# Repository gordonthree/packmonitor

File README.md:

# Smart battery power monitor project

### A slim circuit board for managing charge and discharge of multi-cell LiFePo4 battery packs. Intended to track state of charge by coulomb counting and prevent battery pack damage from over discharge, over current and over temperature conditions.

## Goals:

1. Monitor and record total amperage in and out
2. Monitor and record temperature, ideally three places
3. Monitor and record pack voltage
4. Provide under-voltage disconnect
5. Provide over-temperature disconnect

## Features:
1. Atmel AVR: AVR128DA32 or AVR128DA28
1. Hall effect current sensor: TMCS1108
   * ~~Check my inventory for ACS7xx sensors!~~
3. FRAM for local data caching: I2C FM24C64B
4. Precision ADC: I2C NAU7802
5. Hot swap buffer: I2C TCA4311a / PCA9508 (pin compatible)
1. ~~Host side i2c mux: PCA9545A~~ (hope to avoid)
6. Max PCB width 18mm
7. Precision fixed resistor for thermistors?
   * Thermistors: NRL1504F3950B1F
   * Thermistors connect to uC ADC, 12 bit good 'nuff
8. ~~Power selector IC: AP2411~~
9. Low Iq power supply for battery side, switching, not sure yet!
10. ~~SMT button for battiery status,~~ not sure yet, board is pretty tight

## Connectors:

1. Battery side
   * Battery In and Out (14 ga) - WAGO screw cage
   * 6-pin jst-xh vertical for three thermistors
1. Upstream interface: I2C
   * JST-xh 6-pin connector +5v, GND, SCL, GND, SDA, GND
   * TCA4311 on battery side
   * I2C switch on host side (might not need)

## Indicators (not likely):

1. Bus controlled:
   * Bus power (from vcc)
   * Bus active (from CS line)
2. uC controlled:
   * Battery SOC (three leds)
   * Battery health (red/green)

## Client Commands:

* See registers.md for addressing and more details

## Questions:

1. Data logging without a RTC?
  * Chip seems to keep time well enough with occasional updates from master
1. High side or low side disconnect?

## Resources:

#### ATMega4808:

* [https://www.digikey.com/en/products/detail/microchip-technology/ATMEGA4808-AUR/10444912](https://www.digikey.com/en/products/detail/microchip-technology/ATMEGA4808-AUR/10444912)
* [https://ww1.microchip.com/downloads/en/DeviceDoc/ATmega4808-09-DataSheet-DS40002173C.pdf](https://ww1.microchip.com/downloads/en/DeviceDoc/ATmega4808-09-DataSheet-DS40002173C.pdf)
* [https://github.com/MCUdude/MegaCoreX#pinout](https://github.com/MCUdude/MegaCoreX#pinout)

#### Thermistor:

* [https://www.digikey.com/en/products/detail/eaton-electronics-division/NRL1504F3950B1F/15927588](https://www.digikey.com/en/products/detail/eaton-electronics-division/NRL1504F3950B1F/15927588)
* [https://www.maximintegrated.com/en/design/technical-documents/app-notes/1/1753.html](https://www.maximintegrated.com/en/design/technical-documents/app-notes/1/1753.html)
* [https://www.jameco.com/Jameco/workshop/TechTip/temperature-measurement-ntc-thermistors.html](https://www.jameco.com/Jameco/workshop/TechTip/temperature-measurement-ntc-thermistors.html)

#### Readng precise voltages:

* [https://skillbank.co.uk/arduino/measure.htm](https://skillbank.co.uk/arduino/measure.htm)

#### ATMEGA Arduino:

* [https://github.com/MCUdude/MegaCoreX](https://github.com/MCUdude/MegaCoreX)

#### AVR DA / DB / DD Series:

* [https://github.com/SpenceKonde/DxCore](https://github.com/SpenceKonde/DxCore)
#### Bootloader:

* [https://github.com/Optiboot/optiboot](https://github.com/Optiboot/optiboot)

#### FRAM:

* [FM24C64B](https://www.digikey.com/en/products/detail/cypress-semiconductor-corp/FM24C64B-GTR/3788931)

#### Hall Effect Sensor:

* [https://www.ti.com/product/TMCS1108](https://www.ti.com/product/TMCS1108)

#### Hot swap buffers:

* [https://www.digikey.com/en/products/detail/nxp-usa-inc/PCA9545AD-118/789953](https://www.digikey.com/en/products/detail/nxp-usa-inc/PCA9545AD-118/789953)

* [https://www.ti.com/product/TCA4311A?qgpn=tca4311a](https://www.ti.com/product/TCA4311A?qgpn=tca4311a)
#### Switching regulator (tiny):

* [https://www.diodes.com/assets/Datasheets/AP62200_AP62201_AP62200T.pdf](https://www.diodes.com/assets/Datasheets/AP62200_AP62201_AP62200T.pdf)

#### ADC:

* [https://www.nuvoton.com/export/resource-files/NAU7802%20Data%20Sheet%20V1.7.pdf](https://www.nuvoton.com/export/resource-files/NAU7802%20Data%20Sheet%20V1.7.pdf)

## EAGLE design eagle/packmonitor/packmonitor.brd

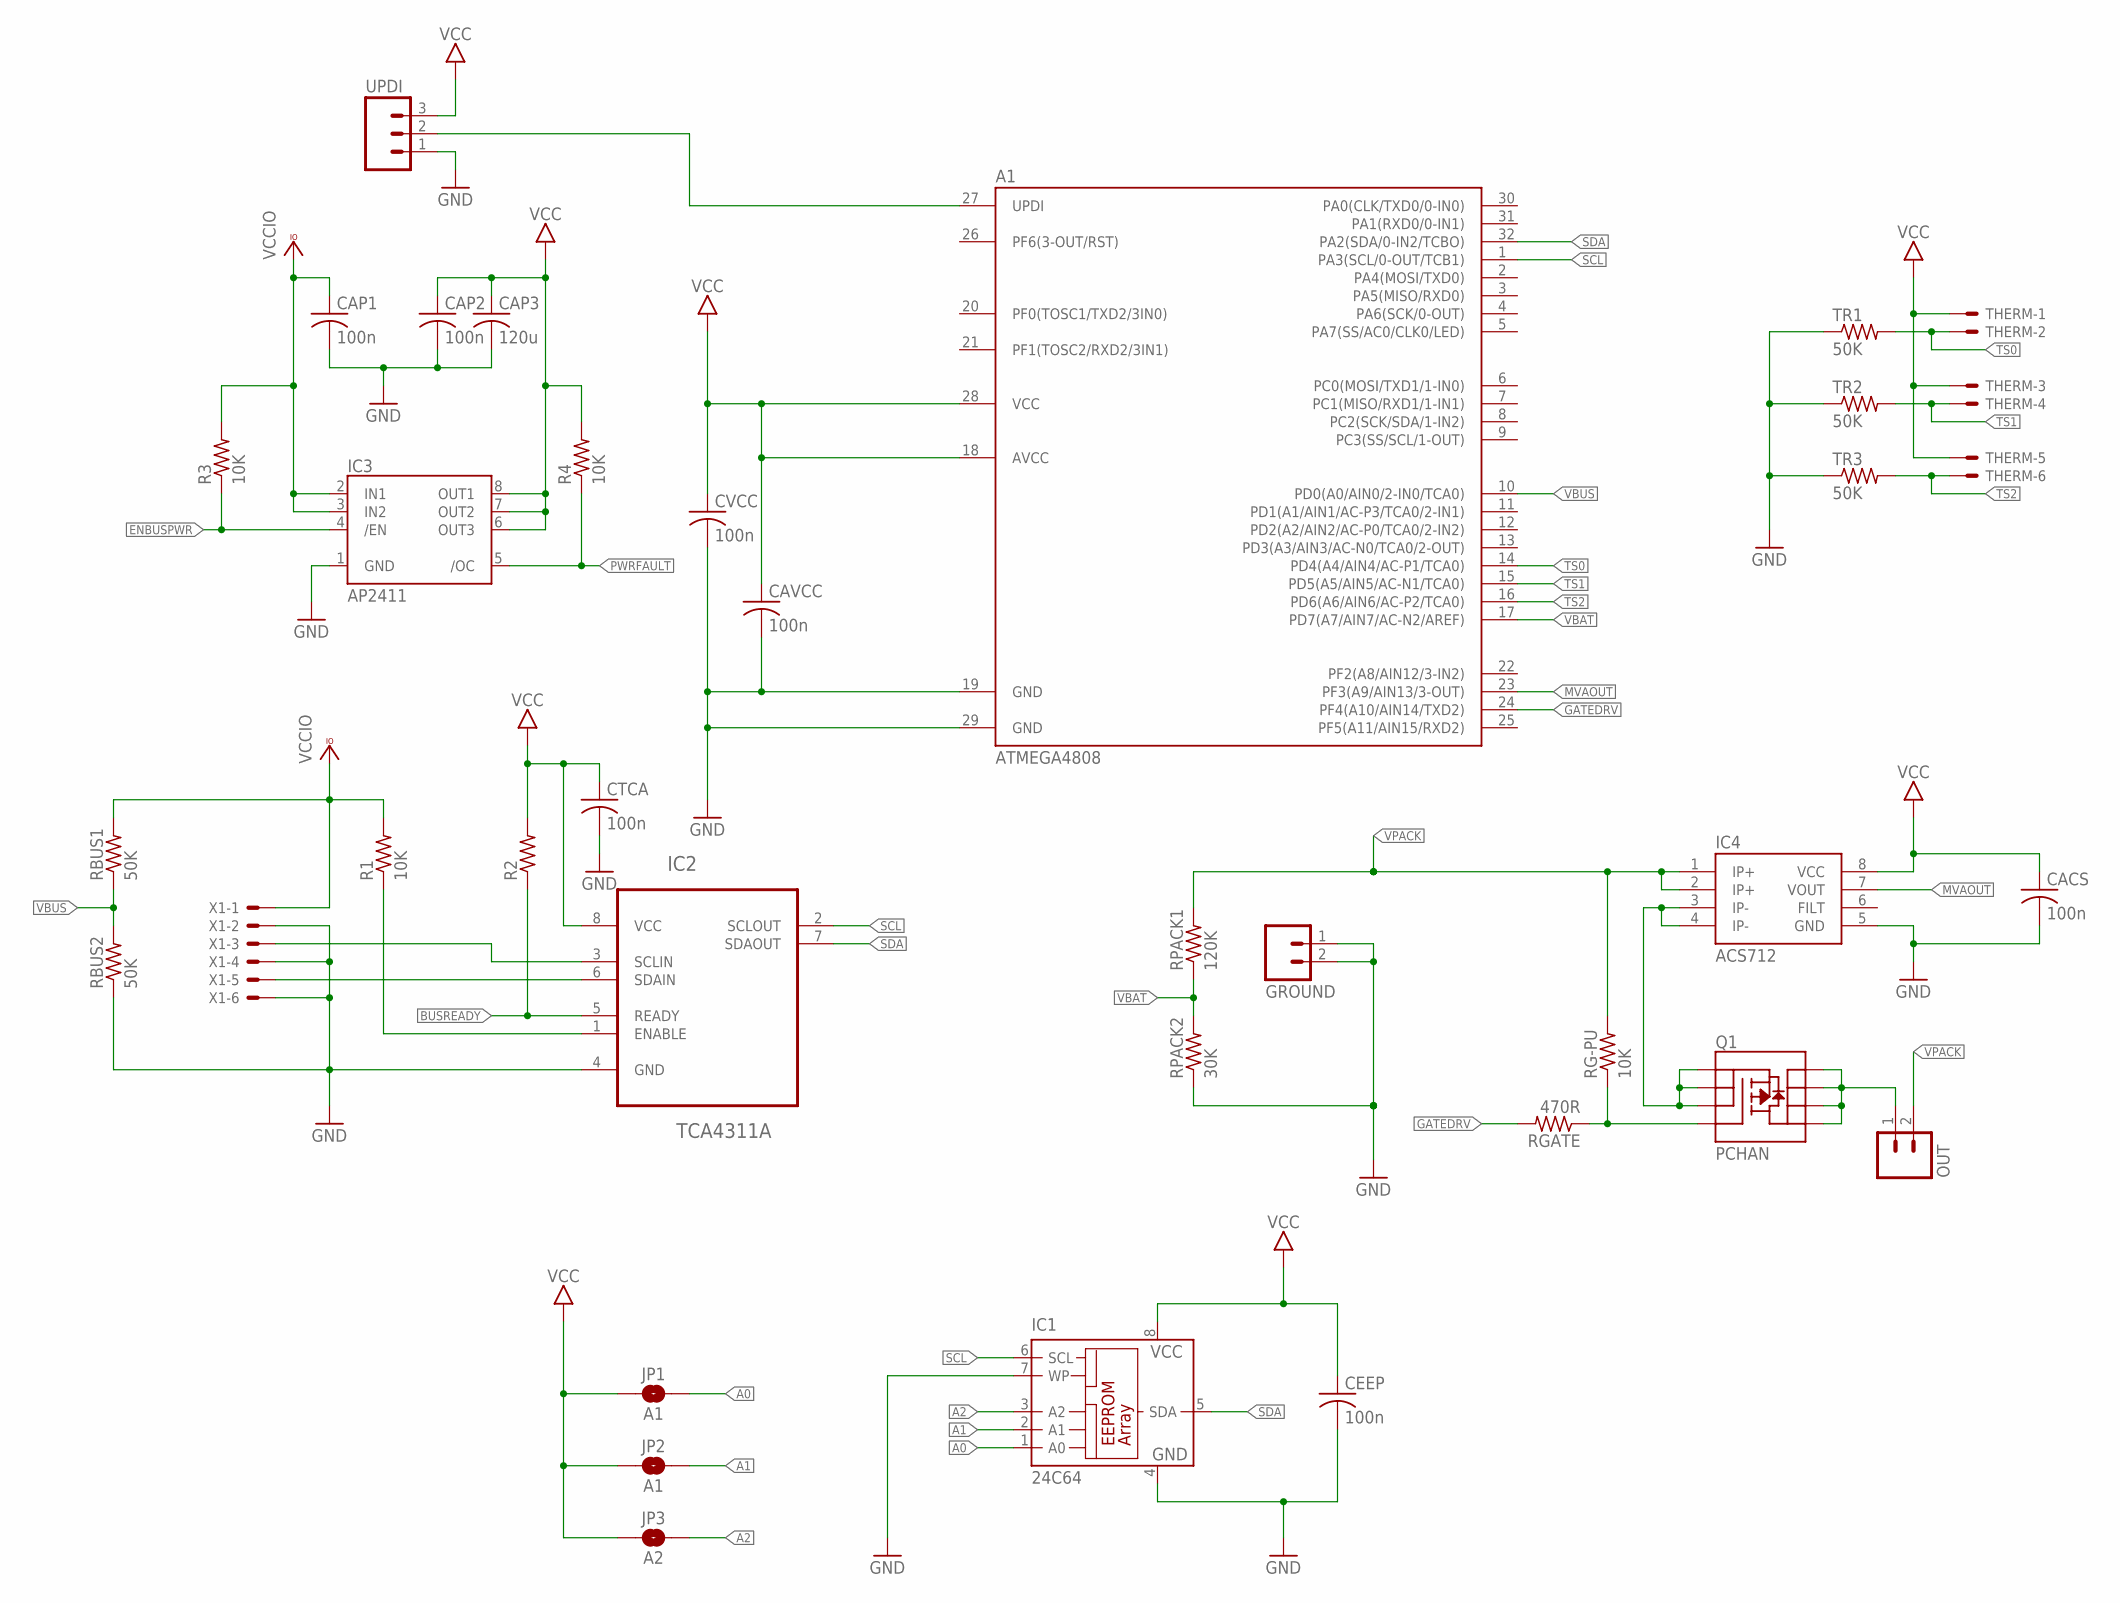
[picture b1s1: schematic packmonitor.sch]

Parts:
A1: ATMEGA4808; TQFP32-08
CACS: 100n; C0603
CAP1, CAP2: 100n; C0603
CAP3: 120u; C1206
CAVCC: 100n; C0603
CEEP: 100n; C0603
CTCA: 100n; C0603
CVCC: 100n; C0603
GROUND: M023.5MM; SCREWTERMINAL-3.5MM-2
IC1: 24C64; SO-08
IC2: TCA4311A; SOIC127P600X175-8N
IC3: AP2411; SO08
IC4: ACS712; SO08
JP1, JP2: A1; SMT-JUMPER_2_NO_SILK
JP3: A2; SMT-JUMPER_2_NO_SILK
OUT: M023.5MM; SCREWTERMINAL-3.5MM-2
Q1: PCHAN; SO08
R1, R3, R4: 10K; R0603
R2: R-US_R0603; R0603
RBUS1, RBUS2: 50K; R0805
RG-PU: 10K; R0603
RGATE: 470R; R0603
RPACK1: 120K; R0805
RPACK2: 30K; R0805
THERM: JST-XH-06-PIN-ROUND-PAD; JST-XH-06-PACKAGE-ROUND-PAD
TR1, TR2, TR3: 50K; R0805
UPDI: M03PTH; 1X03
X1: JST-XH-06-PIN-LONG-PAD; JST-XH-06-PACKAGE-LONG-PAD

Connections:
A0: IC1.1 (A0), JP1.2
A1: IC1.2 (A1), JP2.2
A2: IC1.3 (A2), JP3.2
BUSREADY: IC2.5 (READY), R2.1
ENBUSPWR: IC3.4 (/EN), R3.1
GATE: Q1.4 (G), RG-PU.1, RGATE.1
GATEDRV: A1.24 (PF4(A10/AIN14/TXD2)), RGATE.2
GND: A1.19 (GND), A1.29 (GND), CACS.2, CAP1.2, CAP2.2, CAP3.2, CAVCC.2, CEEP.2, CTCA.2, CVCC.2, GROUND.1, GROUND.2, IC1.4 (GND), IC1.7 (WP), IC2.4 (GND), IC3.1 (GND), IC4.5 (GND), RBUS2.1, RPACK2.1, TR1.1, TR2.1, TR3.1, UPDI.1, X1.2, X1.4, X1.6
MVAOUT: A1.23 (PF3(A9/AIN13/3-OUT)), IC4.7 (VOUT)
unnamed: IC2.6 (SDAIN), X1.5
unnamed: IC2.3 (SCLIN), X1.3
unnamed: IC2.1 (ENABLE), R1.1
P+IN: IC4.3 (IP-), IC4.4 (IP-), Q1.1 (S), Q1.2 (S), Q1.3 (S)
P+OUT: OUT.1, Q1.5 (D), Q1.6 (D), Q1.7 (D), Q1.8 (D)
PWRFAULT: IC3.5 (/OC), R4.1
SCL: A1.1 (PA3(SCL/0-OUT/TCB1)), IC1.6 (SCL), IC2.2 (SCLOUT)
SDA: A1.32 (PA2(SDA/0-IN2/TCBO)), IC1.5 (SDA), IC2.7 (SDAOUT)
TS0: A1.14 (PD4(A4/AIN4/AC-P1/TCA0)), THERM.2, TR1.2
TS1: A1.15 (PD5(A5/AIN5/AC-N1/TCA0)), THERM.4, TR2.2
TS2: A1.16 (PD6(A6/AIN6/AC-P2/TCA0)), THERM.6, TR3.2
UPDI: A1.27 (UPDI), UPDI.2
VBAT: A1.17 (PD7(A7/AIN7/AC-N2/AREF)), RPACK1.1, RPACK2.2
VBUS: A1.10 (PD0(A0/AIN0/2-IN0/TCA0)), RBUS1.1, RBUS2.2
VCC: A1.18 (AVCC), A1.28 (VCC), CACS.1, CAP2.1, CAP3.1, CAVCC.1, CEEP.1, CTCA.1, CVCC.1, IC1.8 (VCC), IC2.8 (VCC), IC3.6 (OUT3), IC3.7 (OUT2), IC3.8 (OUT1), IC4.8 (VCC), JP1.1, JP2.1, JP3.1, R2.2, R4.2, THERM.1, THERM.3, THERM.5, UPDI.3
VCCIO: CAP1.1, IC3.2 (IN1), IC3.3 (IN2), R1.2, R3.2, RBUS1.2, X1.1
VPACK: IC4.1 (IP+), IC4.2 (IP+), OUT.2, RG-PU.2, RPACK1.2

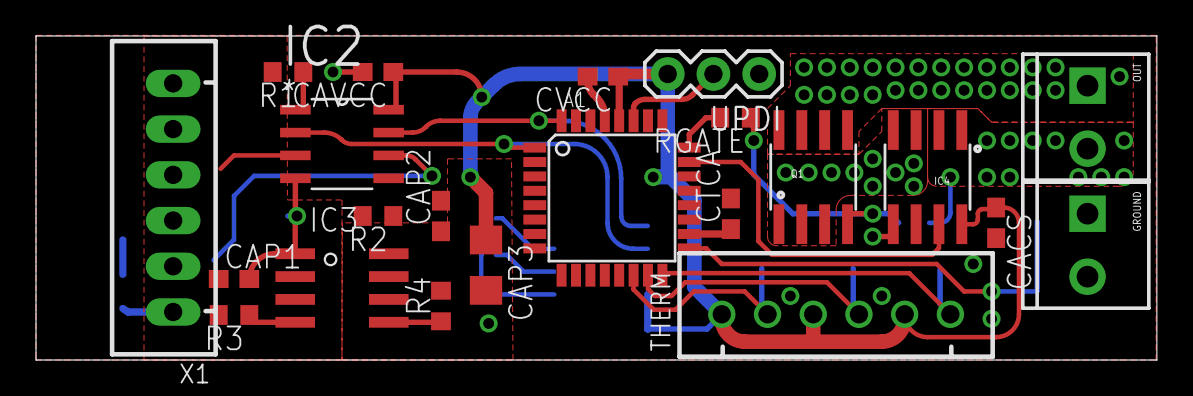
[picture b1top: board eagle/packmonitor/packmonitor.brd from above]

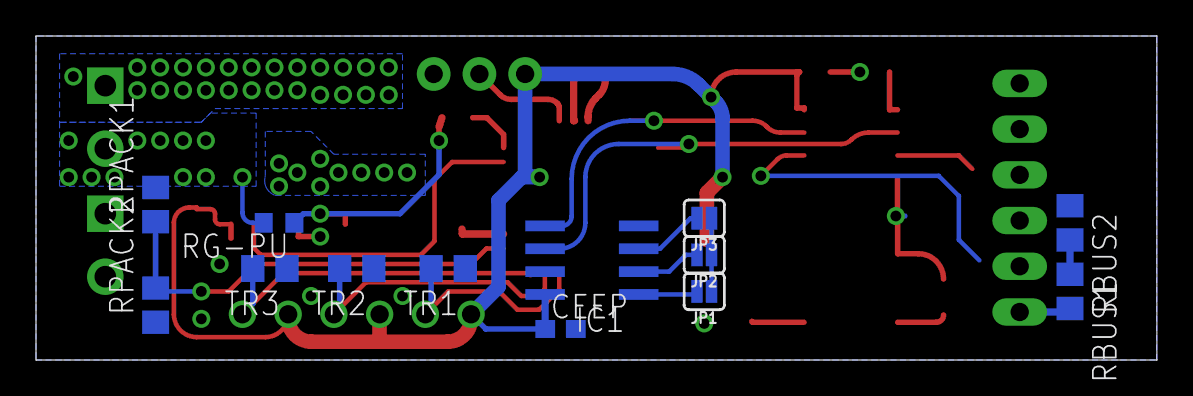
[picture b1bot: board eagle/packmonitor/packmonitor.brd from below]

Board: 2 copper layers, 62.3 x 18.0 mm, 35 parts (13 on the bottom side), 26 nets.

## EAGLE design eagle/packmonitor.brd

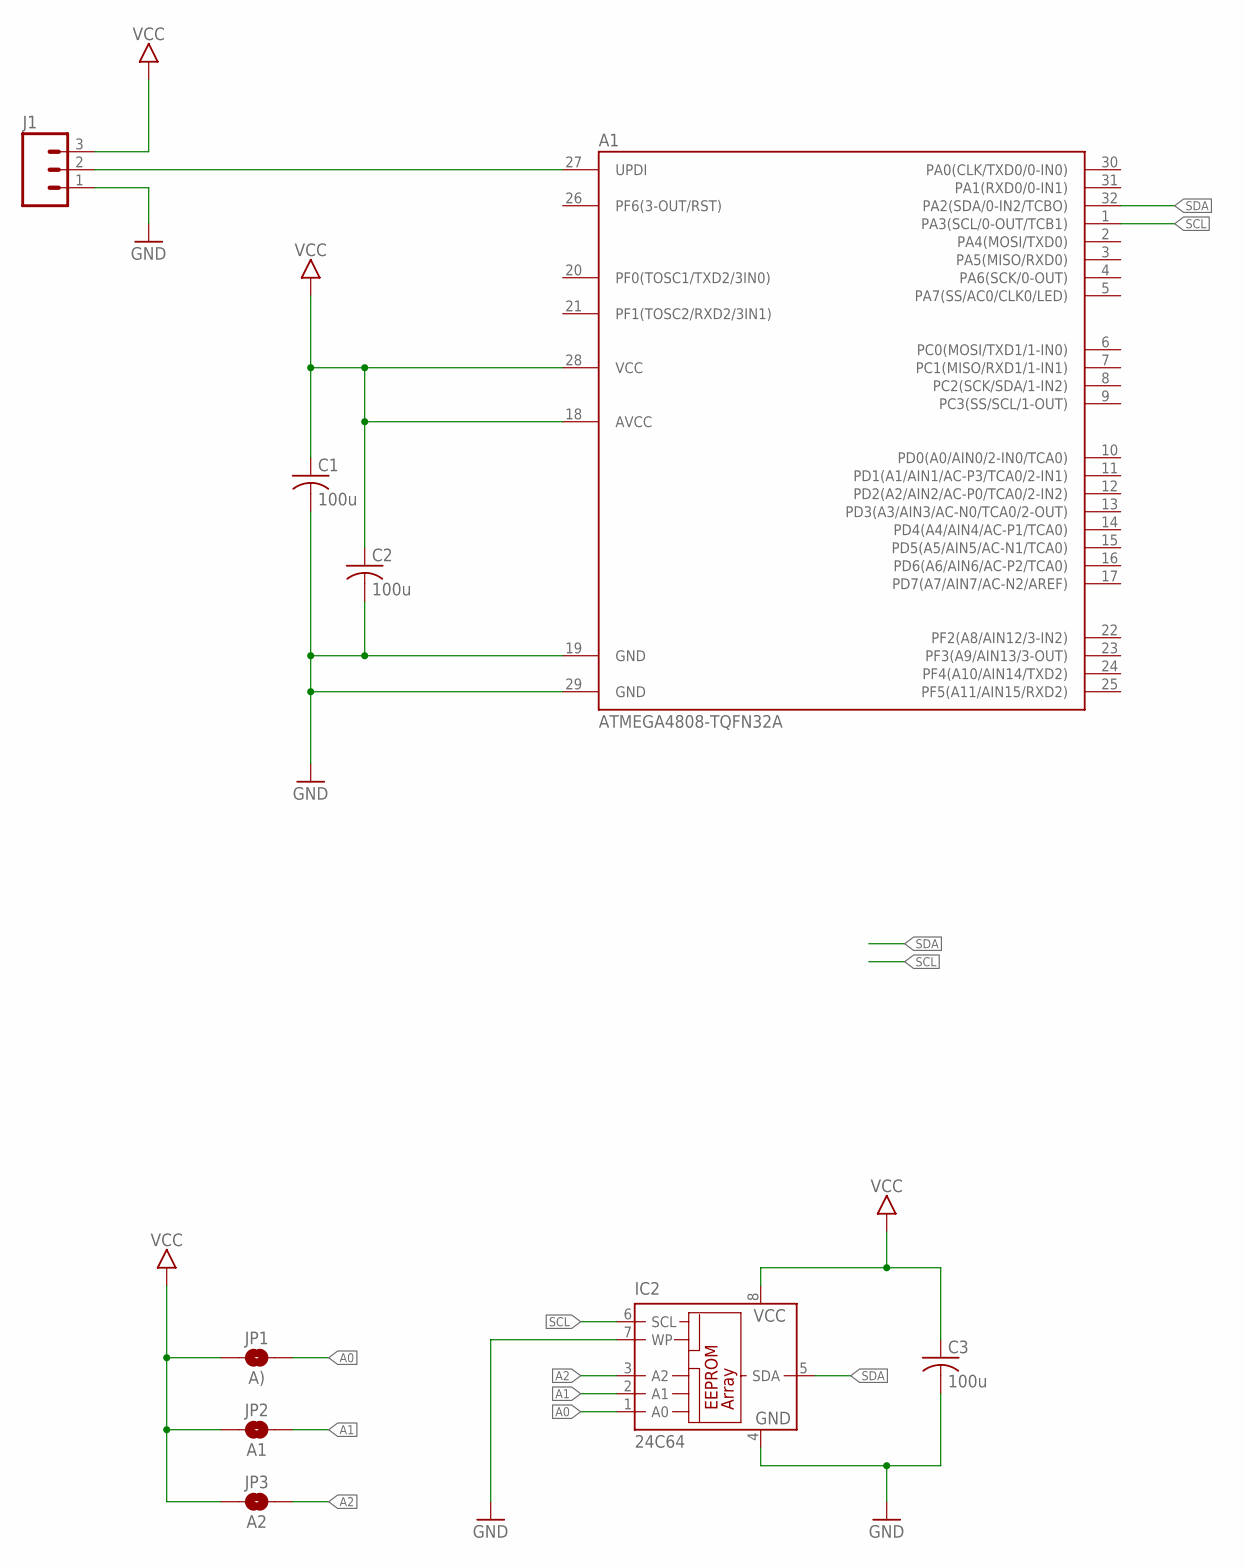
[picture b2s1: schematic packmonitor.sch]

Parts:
A1: ATMEGA4808-TQFN32A; TQFP32-08
C1, C2, C3: 100u; C0603
IC2: 24C64; SO-08
J1: M03LOCK_LONGPADS; 1X03_LOCK_LONGPADS
JP1: A); SMT-JUMPER_2_NO_SILK
JP2: A1; SMT-JUMPER_2_NO_SILK
JP3: A2; SMT-JUMPER_2_NO_SILK

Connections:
A0: IC2.1 (A0), JP1.2
A1: IC2.2 (A1), JP2.2
A2: IC2.3 (A2), JP3.2
GND: A1.19 (GND), A1.29 (GND), C1.2, C2.2, C3.2, IC2.4 (GND), IC2.7 (WP), J1.1
unnamed: A1.27 (UPDI), J1.2
SCL: A1.1 (PA3(SCL/0-OUT/TCB1)), IC2.6 (SCL)
SDA: A1.32 (PA2(SDA/0-IN2/TCBO)), IC2.5 (SDA)
VCC: A1.18 (AVCC), A1.28 (VCC), C1.1, C2.1, C3.1, IC2.8 (VCC), J1.3, JP1.1, JP2.1, JP3.1

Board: 2 copper layers, 9 parts (3 on the bottom side), 8 nets, no tracks yet.

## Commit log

2022-07-28 Updated readme.me
    Copy pasta from Docs to Markdown converter in G-Docs
2022-07-28 Update README.md
    Changed host interface to SPI
2022-07-29 A whole lot of editing, still fleshing out my plan
2022-07-29 added Eagle related files
2022-07-29 added link for logic buffer
2022-07-29 Further refinement
2022-07-29 created vscode workspace
2022-07-29 created empty platformio project
2022-07-29 switched to minicore for mega328p
2022-07-29 das blinken lite
2022-07-29 adding spi slave code, and more LEDs for blinkin
2022-07-29 ignore platformio hdden files and folders
2022-07-29 ignore vscode stuff
2022-07-29 baby steps
2022-07-29 hide stuff!
2022-07-29 spi interrupt firing, but not receiving data yet
2022-07-29 keep trying to figure out the ignore syntax
2022-07-29 more progress on slave mode
2022-07-29 more updates, still trying to exclude vscode and pio folders
2022-07-29 hopefully removed .vscode and .pio from tracking
2022-07-29 clean up and comments
2022-07-29 tweak usb tty upload port
2022-07-29 auto-detect usb port not working, reverting
2022-07-29 clean up and refine comments
2022-07-29 updated build flag to add spi debug led
2022-07-29 enable verbose compile output
2022-07-30 could not make SPI work reliably, now i2c
2022-07-30 fleshing out i2c features
2022-07-30 adding i2c complexity
2022-07-30 fixed event handler typo!
2022-07-30 added basic i2c register writes
2022-07-30 removed spi library include
2022-07-30 created struct to handle incoming data
2022-07-30 adding comments
2022-07-30 created list of registers
2022-07-30 added UnixTime depedency
2022-07-30 Added time lib from Paul Stoffregen
2022-07-30 added unixtime and timelib includes
2022-07-30 adjusted time libraries
2022-07-31 added timestamp related structure and union
2022-07-31 lots to flesh out here
2022-07-31 trying to keep up the docu
2022-07-31 master is able to set slave clock now
2022-07-31 slave timekeeping appears to be working
2022-07-31 docu continues
2022-07-31 switched to switch for event handling
2022-07-31 oops had everything duplicated, renumber some fnc
2022-07-31 adding registers to switch case
2022-07-31 renumbering
2022-07-31 renumbering, adding data types
2022-07-31 added data types
2022-07-31 adding docu
2022-07-31 switch case documented, mostly
2022-07-31 marked shared variables as volatile
2022-07-31 move slow stuff out of the ISR, clean up vars
2022-07-31 needed curly braces inside every case
2022-07-31 forgot %lu to print a timestamp
2022-07-31 clarify docu
2022-07-31 fix typos
2022-07-31 fleshed out most of the commands
2022-07-31 fix some typos
2022-07-31 two way comms now working with master!
2022-07-31 added DXCore Link
2022-07-31 added 4808, updated board for nano
2022-07-31 added uptime tracking and command, cleanup
2022-07-31 added options for different boards
2022-07-31 added build flags for different chips
2022-07-31 moved pins and structs into their own header files
2022-07-31 back to i2c part numbers, add links, move stuff
2022-07-31 added i2c switch for host side
2022-07-31 added struct for adc readings
2022-07-31 added more members to adc struct
2022-07-31 revised comment
2022-07-31 added adc pins for mega328
2022-07-31 tinkering with adc
2022-08-01 renamed files
2022-08-01 ADC reading reliably now, floats working i2c
2022-08-01 going to keep this handy!
2022-08-01 ignore eagle backup files hopefully
2022-08-01 tweaked eagle ignores
2022-08-01 added 4808 mcu
2022-08-01 added for quick reference
2022-08-01 slowly adding parts and putting together layout
2022-08-01 added arduino nano every
2022-08-01 added nano every
2022-08-01 moved the upload_protocol for mega4808
2022-08-01 Successfully compiles for atmega4809 now
2022-08-01 slowly adding components
2022-08-01 updated to include packmonitor sub directory
2022-08-01 Added AP2411S
2022-08-01 making good progress on schematic and board layout
2022-08-01 refined connector choice
2022-08-02 added potential adc docu
2022-08-02 making progress slowly
2022-08-02 A0 seems wonky, shifting to a1-a3
2022-08-02 current and voltage readouts working correctly,
2022-08-02 tweak formatting
2022-08-02 trying to get nan-every working
2022-08-02 made some good progress on the board this afternoon!
2022-08-02 simple typo was stopping slave address build flag, doh
2022-08-02 maybe find the right pin on Every for the built in
2022-08-03 i2c not sending correctly from nanoevery
2022-08-03 documentation updates
2022-08-03 second slave still having issues sending data
2022-08-03 code cleanup
2022-08-04 got floats and ulongs going again
2022-08-04 moved libdeps to the global context
2022-08-04 trying to fix jtag upload for m4809 on nano-every
2022-08-04 script to manually reset Nano Every bootloader
2022-08-04 megacorex finally uploading to nano_every!
2022-08-04 added avr128da28 environment
2022-08-04 fixed pins for 128da28, added pins for 128da32
2022-08-04 added env for 128da32
2022-08-04 trying to get a clean compile for avr128da32
2022-08-04 new branch focusing on DA, removed other envs
2022-08-04 updated pin assignments for DA
2022-08-04 going to shoe-horn dual mode in
2022-08-05 trying to figure out dual mode
2022-08-05 update project scope for AVR DA series
2022-08-05 I think the config works, will find out...
2022-08-05 refine the docu
2022-08-05 latest i2c config code, compiles for both chips
2022-08-05 fix some comments, swap pins around
2022-08-05 back to using macros for sda pins
2022-08-05 added i2c eeprom library includes
2022-08-05 brought over some i2c routines from packmaster
2022-08-05 trying to modularize commonly used functions
2022-08-05 working on new routines
2022-08-05 i2c routines moved into their own library
2022-08-05 switching to my own i2c routines library
2022-08-05 correct led pins for breadboard, update upload
2022-08-05 add packmonlib to lib_eps
2022-08-06 both chips running, serial not working
2022-08-06 platformio custom prog cmd uses variables now
2022-08-06 still trying to get serial working
2022-08-06 frustration maxxed out, nothing works!
2022-08-06 finally got the alias for Serial1 and TWI1 figured
2022-08-07 no closer to getting dual-mode working
2022-08-07 local host finds local clients now!
2022-08-07 added some defaults from arduino boards.txt
2022-08-07 change some build flags
2022-08-07 comment spacing
2022-08-07 still nooo luck
2022-08-07 fiddling, no change
2022-08-08 changed one flag, and dual mode works!
2022-08-08 changed one flag and dual-mode works
2022-08-08 added debug_msg struct
2022-08-09 memcpy instead of strncpy
2022-08-09 moved variable defs into main code body
2022-08-09 making progress again, feels like starting over
2022-08-09 updated a few structs
2022-08-09 clients send raw adc values intead of floats
2022-08-09 add lib deps for eeprom and adc
2022-08-09 add includes for adc and eeprom
2022-08-09 first pass at fram routines
2022-08-09 create a bunch of data conversion routines
2022-08-09 reworking all the ISR switch cases, ugh
2022-08-09 removing unused files
2022-08-10 new fram library apparently
2022-08-10 trim some fat
2022-08-10 rewrote receiveevent isr, new fram library
2022-08-10 fixed a lot of errors, need to fix adc lib
2022-08-10 library headaches
2022-08-10 fixed the adc library
2022-08-10 don't need the rx buffer anymore
2022-08-10 close, but data type problems have returned
2022-08-10 i2c tx and rx seem reliable now!
2022-08-10 added adc conversion routines
2022-08-10 change count to raw, cleanup code
2022-08-10 update the docu
2022-08-10 create defines for the registers
2022-08-10 A lot of register defines created and commented
2022-08-10 tweak the docu
2022-08-10 use double instead of float
2022-08-10 start adding data to fram and memory buffer
2022-08-10 missed changing count to raw in one function
2022-08-10 making progress
2022-08-10 code cleanup, add firstrun check
2022-08-10 add firstrun build flag
2022-08-11 moved all static defines to their own file
2022-08-11 cleared firstrun build flag
2022-08-11 starting to tinker with external adc
2022-08-11 increase raw size to 32 bit
2022-08-11 clean up code
2022-08-11 added registers for voltage and current sense cfg
2022-08-11 fix typo
2022-08-11 added new registers
2022-08-11 another new register
2022-08-11 added registors and routines
2022-08-11 tweak temp warning
2022-08-11 moved files to proper directories
2022-08-11 added bus voltage status
2022-08-11 more changes for monitoring and control
2022-08-11 fix a typo
2022-08-11 register tweaks
2022-08-11 so many additions!
2022-08-12 updated organization, added util funcs
2022-08-12 fixed addressing error, add util funcs
2022-08-12 added ability to directly dump eeprom contents
2022-08-12 static const!
2022-08-12 removed trailing space
2022-08-12 addbytearray doesn't work
2022-08-12 futz around with structures and sizes
2022-08-12 so many changes
2022-08-12 fixed some size mismatches
2022-08-12 fix logic errors in the update routine
2022-08-12 reset on bad i2c scan, pack voltage logic
2022-08-12 fixed eeprom address bug hopefully
2022-08-12 tweak dump eeprom buffer routine
2022-08-12 fix incorrect type for getRaw
2022-08-12 fixed incorrect type for getRaw
2022-08-12 dump saves and rereads fram
2022-08-12 save after add, eliminate redundant unions
2022-08-12 named the unions
2022-08-12 removed fram handling, fixed add array bug
2022-08-12 added fram save/load, fram finally works
2022-08-12 set current time from last saved time on boot
2022-08-12 reset alarm counts
2022-08-12 added in-ram buffer for temperature readings
2022-08-12 created struct for temperature readings
2022-08-12 tweak struct, add semicolon
2022-08-12 debug status reg reads
2022-08-13 organization, fixed startup status0
2022-08-13 changed usb ports after reboot
2022-08-13 moved ntc lut
2022-08-13 cleanup, created framDump fn
2022-08-13 added reset command note
2022-08-13 comment formatting
2022-08-13 groundwork for multiregister read support
2022-08-13 increase buffer size to 127 bytes
2022-08-13 big changes, only send entire registers
2022-08-13 renumber some registers, some are deprecated
2022-08-14 renumber and reoganize registers
2022-08-14 float / double causing issues on esp8266
2022-08-14 timeSet not a function, trim fns
2022-08-14 removed leftover #endif
2022-08-14 replace double with float, update temp defaults
2022-08-14 temp high/low memory issues
2022-08-14 much good progress
2022-08-14 change to sparkfun adc library
2022-08-16 internal adc for everything, seems good now
2022-08-16 update raw fns to include sysvcc
2022-08-16 six adc now!
2022-08-16 remove external adc library
2022-08-16 ok i guess
2022-08-16 delted local copy of library
2022-08-16 added more status registers
2022-08-16 corrected sysvcc
2022-08-16 removed unused fns
2022-08-16 organize defs, removed unused defs
2022-08-16 update defs and docu
2022-08-16 track high/low bus voltage
2022-08-16 organize defs
2022-08-17 comments, i2c rx/tx diags on, repl double wtih flo
2022-08-17 store readings even if they are in error state
2022-08-17 turned off debugging prints
2022-08-17 tweaks, code cleanup
2022-08-18 uptime counter works now
2022-08-19 updated pin assignments to match schematic
2022-08-22 switch to 12-bit ADC values
2022-08-22 com ports moved after reboot
2022-08-22 reverted back to 10bit adc for temps

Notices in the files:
parts and their libraries:
SparkFun-Jumpers: Licensing: Creative Commons ShareAlike 4.0 International - https://creativecommons.org/licenses/by-sa/4.0
